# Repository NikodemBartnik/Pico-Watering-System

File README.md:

## Video

Simple automated solar powered watering system for your garden based on cool and inexpensive [Raspberry Pi Pico](https://www.raspberrypi.com/products/raspberry-pi-pico/). 
Designed by [Nikodem Bartnik](https://www.youtube.com/nikodembartnik). 

Most important features of this system

  - Simplicity
  - Watering based on time adjusted with buttons and current setting diplayed with LEDs
  - Ability to adjust watering cycles per day (1-4) and watering time (2,4,6,8 minutes per cycle) both values can be edjusted in the code
  - Single sided PCB that's easy to make at home
  - 2 water level sensors, 2 pumps and 2 soil moisture sensors to run two separete systems for different parts of the garden
  - Pumps controlled with IRFZ44N MOSFETs
  - Easy to 3D print case for the system
  - Beginner friendly

## Open Source
This project is open source, feel free to build, modify adjust to your needs and don't forget to share the results with others! I welcome everyone to improve it and contribute to the project!

## Parts

|   Name    |   Amazon   |  Aliexpress  |
|   ------- |   ----    | ------------  |
| Raspberry Pi Pico | https://amzn.to/3O2GBdG | https://bit.ly/3c9K7FP |
| Solar panel and charger | https://amzn.to/3PqgpLp | https://bit.ly/3yDzbIe |
| Garden irrigation set | https://amzn.to/3uLS3DL | https://bit.ly/3c9sE0m |
| Battery | https://amzn.to/3ceAIx6 | - |
| Pump | https://amzn.to/3O74vF0 | https://bit.ly/3z0th5v |
| Water level sensor | https://amzn.to/3z16nL9 | https://bit.ly/3nVWZSD |
| IRFZ44N | https://amzn.to/3O1NyvJ | https://bit.ly/3aG8udU |
| LEDs | https://amzn.to/3yxl1Zj | https://bit.ly/3NZ0nXz | 
| Buttons | https://amzn.to/3z0r75T | https://bit.ly/3yD8UtK |

You will also need a PCB to solder all the components, [prefboard](https://amzn.to/3RsRubK) if you don't want to make a PCB or a [breadboard](https://amzn.to/3P7sjdo). PCB is designed to be machined on a CNC machine, the traces are a bit thicker than normal and it is single sided. You can also easily make it at home using different manufacturing techniques, of course ordering it from professional  manufacturers is also an option.

## Support
You can support my projects on [Patreon](https://www.patreon.com/nikodembartnik) and [PayPal](https://paypal.me/nikodembartnik).
Here is my online store with parts for [IndyMill](https://github.com/NikodemBartnik/IndyMill) a CNC machine that I designed.

***

You can also checkout WDCS (Watering and Data Collection System) mentioned in the video. It's a more sophisticated solution with more sensor that you probably don't even need :) I suggest to stick to the Pico version because it is much better!

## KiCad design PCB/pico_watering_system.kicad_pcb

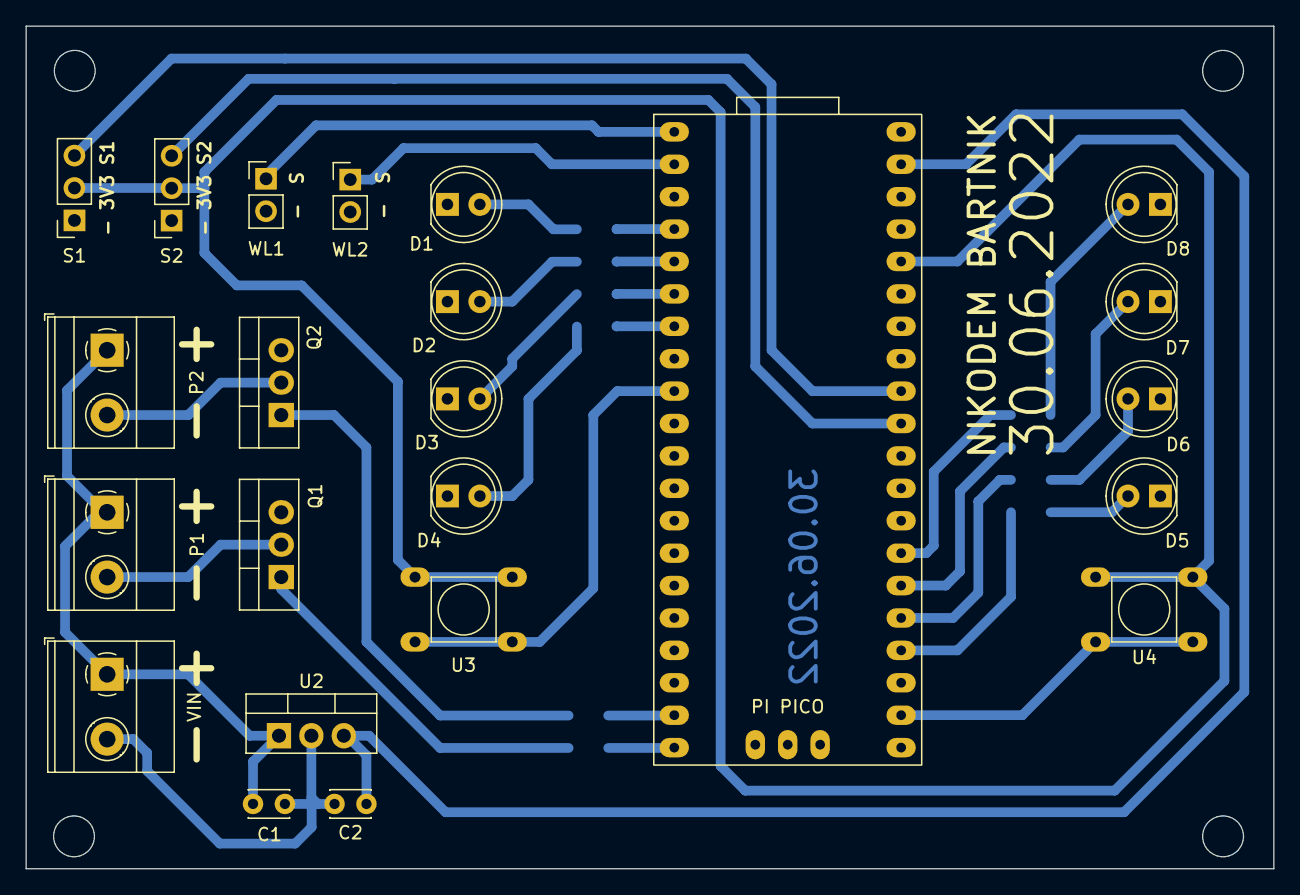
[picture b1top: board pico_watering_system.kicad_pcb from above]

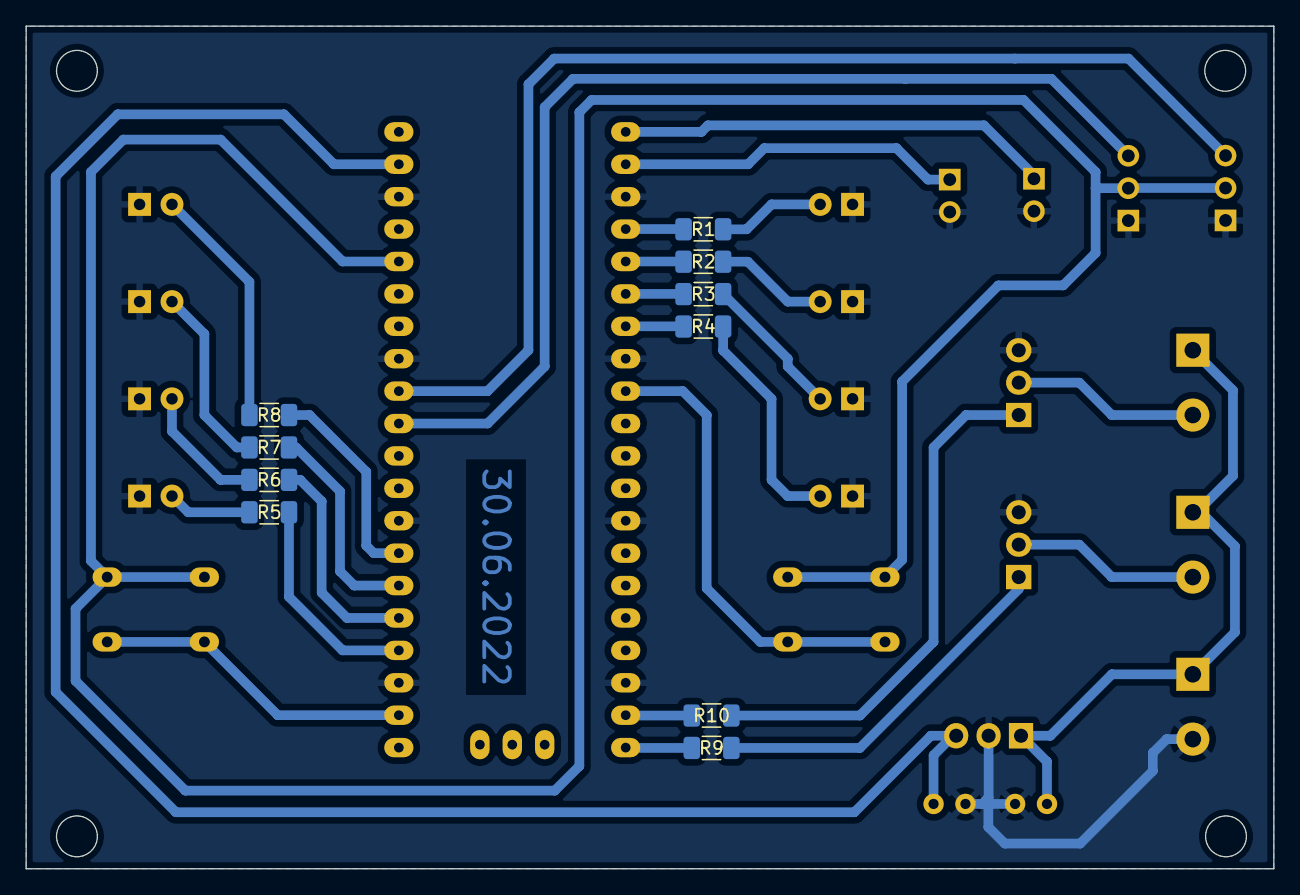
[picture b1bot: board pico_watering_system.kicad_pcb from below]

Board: 2 copper layers, 97.8 x 66.0 mm, 33 parts (10 on the bottom side), 32 nets.

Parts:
C1: 100u; C_Disc_D3.0mm_W2.0mm_P2.50mm
C2: 10u; C_Disc_D3.0mm_W2.0mm_P2.50mm
D1, D2, D3, D4, D5, D6, D7, D8: LED; LED_D5.0mm
P1: P1; TerminalBlock_Phoenix_MKDS-1,5-2-5.08_1x02_P5.08mm_Horizont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
P2: P2; TerminalBlock_Phoenix_MKDS-1,5-2-5.08_1x02_P5.08mm_Horizont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
PI PICO: pi pico; raspberry pi pico
Q1, Q2: IRFZ44N; TO-220-3_Vertical
R1, R2, R3, R4: 330; R_1206_3216Metric_Pad1.30x1.75mm_HandSolder
R5, R6, R7, R8: 250; R_1206_3216Metric_Pad1.30x1.75mm_HandSolder
R9, R10: 10k; R_1206_3216Metric_Pad1.30x1.75mm_HandSolder
S1: s1; PinSocket_1x03_P2.54mm_Vertical
S2: s2; PinSocket_1x03_P2.54mm_Vertical
U2: L7805; TO-220-3_Vertical
U3, U4: tact_switch
VIN: IN; TerminalBlock_Phoenix_MKDS-1,5-2-5.08_1x02_P5.08mm_Horizont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
WL1: Water level sensor 1; PinHeader_1x02_P2.54mm_Vertical
WL2: Water level sensor 2; PinHeader_1x02_P2.54mm_Vertical

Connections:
+3V3: PI PICO.36 (3V3(OUT)), S1.2, S2.2, U3.1, U3.2, U4.1, U4.2
+5V: C2.1, PI PICO.39 (VSYS), U2.3 (OUT)
+12V: C1.1, P1.1, P2.1, U2.1 (IN), VIN.1
BUTTON1: PI PICO.9 (GP6), U3.3, U3.4
BUTTON2: PI PICO.22 (GP17), U4.3, U4.4
GND: C1.2, C2.2, D1.1 (K), D2.1 (K), D3.1 (K), D4.1 (K), D5.1 (K), D6.1 (K), D7.1 (K), D8.1 (K), PI PICO.3 (GND), PI PICO.8 (GND), PI PICO.13 (GND), PI PICO.18 (GND), PI PICO.23 (GND), PI PICO.28 (GND), PI PICO.33 (GND), PI PICO.38 (GND), Q1.3 (S), Q2.3 (S), S1.1, S2.1, U2.2 (GND), VIN.2, WL1.2, WL2.2
LED_G1: PI PICO.24 (GP18), R5.1
LED_G2: PI PICO.25 (GP19), R6.1
LED_G3: PI PICO.26 (GP20), R7.1
LED_G4: PI PICO.27 (GP21), R8.1
LED_R1: PI PICO.4 (GP2), R1.1
LED_R2: PI PICO.5 (GP3), R2.1
LED_R3: PI PICO.6 (GP4), R3.1
LED_R4: PI PICO.7 (GP5), R4.1
unnamed: D1.2 (A), R1.2
unnamed: D2.2 (A), R2.2
unnamed: D3.2 (A), R3.2
unnamed: D4.2 (A), R4.2
unnamed: D5.2 (A), R5.2
unnamed: D6.2 (A), R6.2
unnamed: D7.2 (A), R7.2
unnamed: D8.2 (A), R8.2
unnamed: P1.2, Q1.2 (D)
unnamed: P2.2, Q2.2 (D)
unnamed: Q1.1 (G), R9.1
unnamed: Q2.1 (G), R10.1
PUMP1: PI PICO.20 (GP15), R9.2
PUMP2: PI PICO.19 (GP14), R10.2
S1: PI PICO.32 (GP27), S1.3
S2: PI PICO.31 (GP26), S2.3
WATER_LEVEL_SENSOR1: PI PICO.1 (GP0), WL1.1
WATER_LEVEL_SENSOR2: PI PICO.2 (GP1), WL2.1

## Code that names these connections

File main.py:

from machine import Pin, ADC, Timer
import time, os

#constants
PIN_PUMP_1 = 15
PIN_PUMP_2 = 14
PIN_LED_R_1 = 2
PIN_LED_R_2 = 3
PIN_LED_R_3 = 4
PIN_LED_R_4 = 5
PIN_LED_G_1 = 18
PIN_LED_G_2 = 19
PIN_LED_G_3 = 20
PIN_LED_G_4 = 21

PIN_BUTTON_1 = 6
PIN_BUTTON_2 = 17

PIN_WATER_LEVEL_SENSOR_1 = 0
PIN_WATER_LEVEL_SENSOR_2 = 1

WATERING_CYCLE_TIMES_ARRAY = [2, 4, 6, 8] #time in minutes

#global variables
selectionActive = True
dailyWateringCycles = 3 
wateringCycleTime = 1 #choose from WATERING_CYCLE_TIMES
selectionTimer = Timer()
lastWatering = time.time()

pump1 = Pin(PIN_PUMP_1, Pin.OUT)
pump2 = Pin(PIN_PUMP_2, Pin.OUT)

ledR1 = Pin(PIN_LED_R_1, Pin.OUT)
ledR2 = Pin(PIN_LED_R_2, Pin.OUT)
ledR3 = Pin(PIN_LED_R_3, Pin.OUT)
ledR4 = Pin(PIN_LED_R_4, Pin.OUT)
ledG1 = Pin(PIN_LED_G_1, Pin.OUT)
ledG2 = Pin(PIN_LED_G_2, Pin.OUT)
ledG3 = Pin(PIN_LED_G_3, Pin.OUT)
ledG4 = Pin(PIN_LED_G_4, Pin.OUT)

button1 = Pin(PIN_BUTTON_1, Pin.IN, Pin.PULL_DOWN)
button2 = Pin(PIN_BUTTON_2, Pin.IN, Pin.PULL_DOWN)
wl1 = Pin(PIN_WATER_LEVEL_SENSOR_1, Pin.IN, Pin.PULL_UP)
wl2 = Pin(PIN_WATER_LEVEL_SENSOR_2, Pin.IN, Pin.PULL_UP)


def checkKeys():
    global selectionActive
    if(button1.value() or button2.value()):
        selectionActive = True
        selectionTimer.init(mode=Timer.ONE_SHOT, period=10000, callback=disableSelection)
        
def disableSelection(t):
    global selectionActive
    selectionActive = False
    ledR1.value(0)
    ledR2.value(0)
    ledR3.value(0)
    ledR4.value(0)
    ledG1.value(0)
    ledG2.value(0)
    ledG3.value(0)
    ledG4.value(0)
    saveSettings()
    selectionTimer.init(mode=Timer.PERIODIC, freq=0.1, callback=signOfLife)
    
    
def saveSettings():
    #saving settings
    try:
        os.remove('t.txt')
    except OSError:
        print("t.txt doesn't exists")
    try:
        os.remove('c.txt')
    except OSError:
        print("t.txt doesn't exists")
        
    f = open('t.txt', 'w+')
    f.write(str(wateringCycleTime))
    f.close()
    f = open('c.txt', 'w+')
    f.write(str(dailyWateringCycles))
    f.close()
    
def loadSettings():
    global wateringCycleTime, dailyWateringCycles
    try:
        f = open('t.txt')
        wateringCycleTime = int(f.read())
        print('wateringCycleTime', wateringCycleTime)
        f.close()
    except OSError:
        print("t.txt doesn't exists")
    try: 
        f = open('c.txt')
        dailyWateringCycles = int(f.read())
        print('dailyWateringCycles', dailyWateringCycles)
        f.close()
    except OSError:
        print("c.txt doesn't exists")

    
def displayWateringTimes():
    if(selectionActive):
        ledR4.value(1) if wateringCycleTime >= 0 else ledR4.value(0)
        ledR3.value(1) if wateringCycleTime >= 1 else ledR3.value(0)
        ledR2.value(1) if wateringCycleTime >= 2 else ledR2.value(0)
        ledR1.value(1) if wateringCycleTime >= 3 else ledR1.value(0)
        
        
def displayWateringCycles():
    if(selectionActive):
        ledG1.value(1) if dailyWateringCycles >= 0 else ledG1.value(0)
        ledG2.value(1) if dailyWateringCycles >= 1 else ledG2.value(0)
        ledG3.value(1) if dailyWateringCycles >= 2 else ledG3.value(0)
        ledG4.value(1) if dailyWateringCycles >= 3 else ledG4.value(0)
    

def checkAndModifySettings():
    global wateringCycleTime, dailyWateringCycles
    if(button1.value()):
        time.sleep_ms(50)
        if(button1.value()):
            wateringCycleTime = (wateringCycleTime+1) if wateringCycleTime < 3 else 0
            displayWateringTimes()
            time.sleep_ms(200)
    
    if(button2.value()):
        time.sleep_ms(50)
        if(button2.value()):
            dailyWateringCycles = (dailyWateringCycles+1) if dailyWateringCycles < 3 else 0
            displayWateringCycles()
            time.sleep_ms(200)
            
            

def checkWatering():
    global lastWatering
    if((time.time() - lastWatering) > (86400/(dailyWateringCycles + 1))):
        wateringStart = time.time()
        if(checkWaterLevel()):
            pump1.value(1)
            while(time.time() - wateringStart < (WATERING_CYCLE_TIMES_ARRAY[wateringCycleTime]*60)):
                ledG1.value(1)
                time.sleep_ms(200)
                ledG1.value(0)
                time.sleep_ms(200)
            pump1.value(0)
        lastWatering = time.time()
        
        
def signOfLife(t):
    ledR1.value(1)
    time.sleep_ms(10)
    ledR1.value(0)
    print('sign of life')
    
def checkWaterLevel():
    return 0 if wl1.value() else 1


def checkWaterAndAlarm():
    if(checkWaterLevel() == 0):
        ledR4.value(1)
        time.sleep_ms(500)
        ledR4.value(0)
        time.sleep_ms(500)
        

#loading the settings from flash before entering the loop
loadSettings()
#disable LEDs after 10 seconds
selectionTimer.init(mode=Timer.ONE_SHOT, period=10000, callback=disableSelection)

while(1):
    checkKeys()
    checkWatering()
    if(selectionActive):
        checkAndModifySettings()
        displayWateringTimes()
        displayWateringCycles()
    else:
        checkWaterAndAlarm()
        
    time.sleep_ms(50)

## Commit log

2022-07-13 readme update
